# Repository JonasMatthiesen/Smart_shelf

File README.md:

# Smart_shelf
All the smart shelf coding needs

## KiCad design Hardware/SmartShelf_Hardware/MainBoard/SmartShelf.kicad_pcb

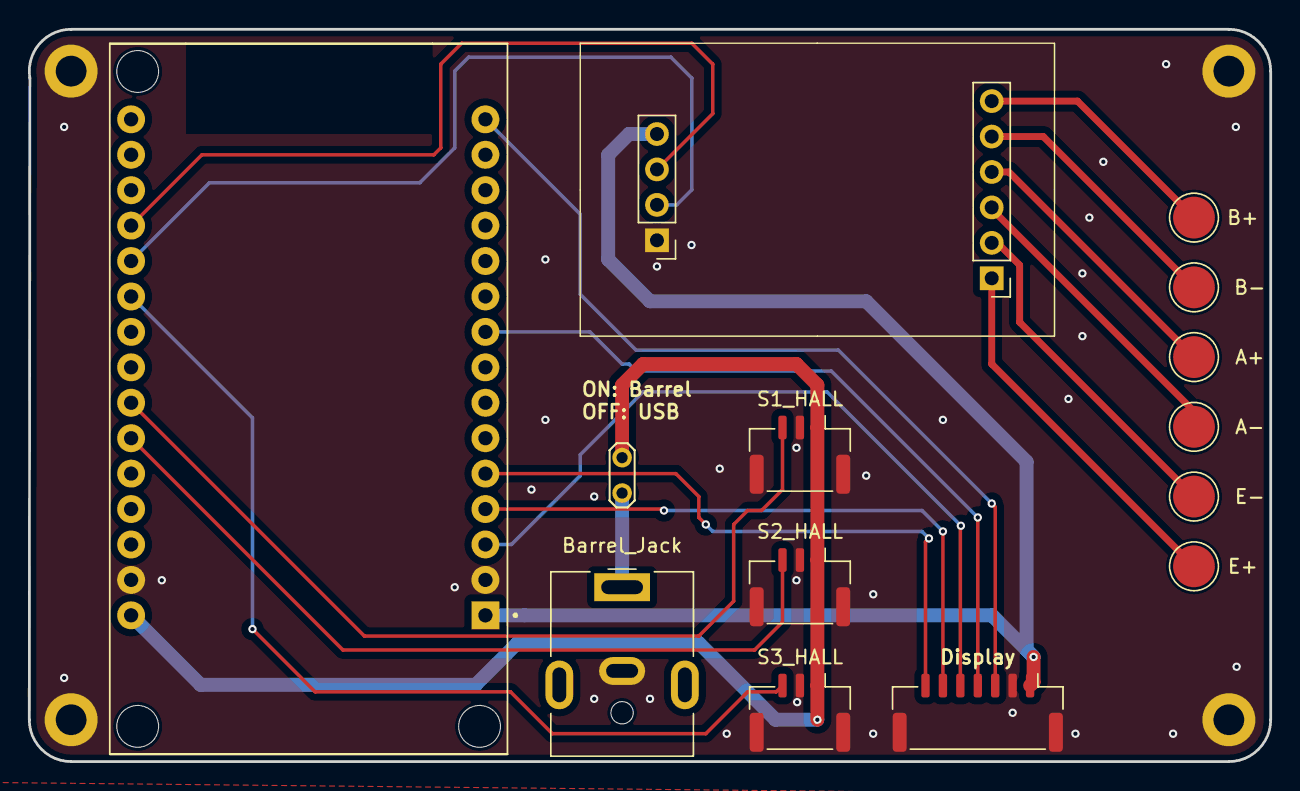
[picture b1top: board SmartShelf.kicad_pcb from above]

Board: 2 copper layers, 89.0 x 52.5 mm, 18 parts (0 on the bottom side), 20 nets.

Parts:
H1, H2, H3, H4: MountingHole_Pad; MountingHole_2.2mm_M2_DIN965_Pad
H5: E+; TestPoint_Pad_D3.0mm
H6: E-; TestPoint_Pad_D3.0mm
H7: A-; TestPoint_Pad_D3.0mm
H8: A+; TestPoint_Pad_D3.0mm
H9: B+; TestPoint_Pad_D3.0mm
H10: B-; TestPoint_Pad_D3.0mm
J1: Display; JST_GH_BM07B-GHS-TBT_1x07-1MP_P1.25mm_Vertical
J3: Barrel_Jack; BarrelJack_CUI_PJ-063AH_Horizontal
J4: S1_HALL; JST_GH_BM03B-GHS-TBT_1x03-1MP_P1.25mm_Vertical
J5: S2_HALL; JST_GH_BM03B-GHS-TBT_1x03-1MP_P1.25mm_Vertical
J6: S3_HALL; JST_GH_BM03B-GHS-TBT_1x03-1MP_P1.25mm_Vertical
JP1: PWR_SEL; TestPoint_2Pads_Pitch2.54mm_Drill0.8mm
U1: HX711Dev
U2: ESP32-DEVKIT-V1; MODULE_ESP32_DEVKIT_V1

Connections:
+3V3: J1.1, U1.10 (VCC), U2.1 (3V3)
+5V: J4.1, J5.1, J6.1, JP1.2 (B), U2.30 (VIN)
/OLED_CLK: J1.4, U2.9 (D18)
/OLED_CS: J1.5, U2.3 (D15)
/OLED_DC: J1.6, U2.4 (D2)
/OLED_DIN/SDA: J1.3, U2.15 (D23)
/OLED_RST: J1.7, U2.5 (D4)
/S1_HALL: J4.3, U2.24 (D26)
/S2_HALL: J5.3, U2.25 (D27)
/S3_HALL: J6.3, U2.21 (D32)
GND: H1.1, H2.1, H3.1, H4.1, J1.2, J1.MP (MountPin), J3.2, J4.2, J4.MP (MountPin), J5.2, J5.MP (MountPin), J6.2, J6.MP (MountPin), U1.7 (GND), U2.2 (GND), U2.29 (GND)
unnamed: J3.1, JP1.1 (A)
unnamed: H8.1, U1.4 (A+)
unnamed: H7.1, U1.3 (A-)
unnamed: H9.1, U1.6 (B+)
unnamed: H10.1, U1.5 (B-)
unnamed: U1.8 (DT), U2.20 (D35)
unnamed: H5.1, U1.1 (E+)
unnamed: H6.1, U1.2 (E-)
unnamed: U1.9 (SCK), U2.19 (D34)

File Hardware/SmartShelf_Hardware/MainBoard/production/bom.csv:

Designator,Footprint,Quantity,Value,LCSC Part #
J1,JST_GH_BM07B-GHS-TBT_1x07-1MP_P1.25mm_Vertical,1,Display,BM07B-GHS-TBT(LF)(SN)
J3,BarrelJack_CUI_PJ-063AH_Horizontal,1,Barrel_Jack,
J4,JST_GH_BM03B-GHS-TBT_1x03-1MP_P1.25mm_Vertical,1,S1_HALL,C161691
J5,JST_GH_BM03B-GHS-TBT_1x03-1MP_P1.25mm_Vertical,1,S2_HALL,BM03B-GHS-TBT(LF)(SN)
J6,JST_GH_BM03B-GHS-TBT_1x03-1MP_P1.25mm_Vertical,1,S3_HALL,BM03B-GHS-TBT(LF)(SN)
JP1,TestPoint_2Pads_Pitch2.54mm_Drill0.8mm,1,PWR_SEL,
U1,HX711Dev,1,~,
U2,MODULE_ESP32_DEVKIT_V1,1,ESP32-DEVKIT-V1,

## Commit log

2025-02-26 Added PCBs
2025-02-26 initial project build
2025-02-26 FAILED: shelf_core.elf
2025-02-26 Fix thread issues and cleanup
2025-02-26 gitignore
2025-03-04 Wifi provision added and MQTT connection established (send only)
2025-03-08 Display done
2025-03-09 can also receive now an are running on a eu-west-1 region
2025-03-09 Weigght sensor done, and init sequence on Shelf_controller done
2025-03-10 Build fixed
2025-03-10 MQTT is now using Grimstads broker
2025-03-17 Changes to support 3 shelfes
2025-03-19 Minor tweaks
2025-03-19 minor change
2025-03-19 added common.h functions to link up with shelf controller
2025-03-24 Added cloud folder and removed all FreeRTOS example
2025-03-24 Added all the backend and frontend scripts
2025-03-26 edit after demo attempt....
